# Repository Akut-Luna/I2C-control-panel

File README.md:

# I2C-control-panel
Modular panels using the MCP23017 IO expansion board and the I2C protocol.

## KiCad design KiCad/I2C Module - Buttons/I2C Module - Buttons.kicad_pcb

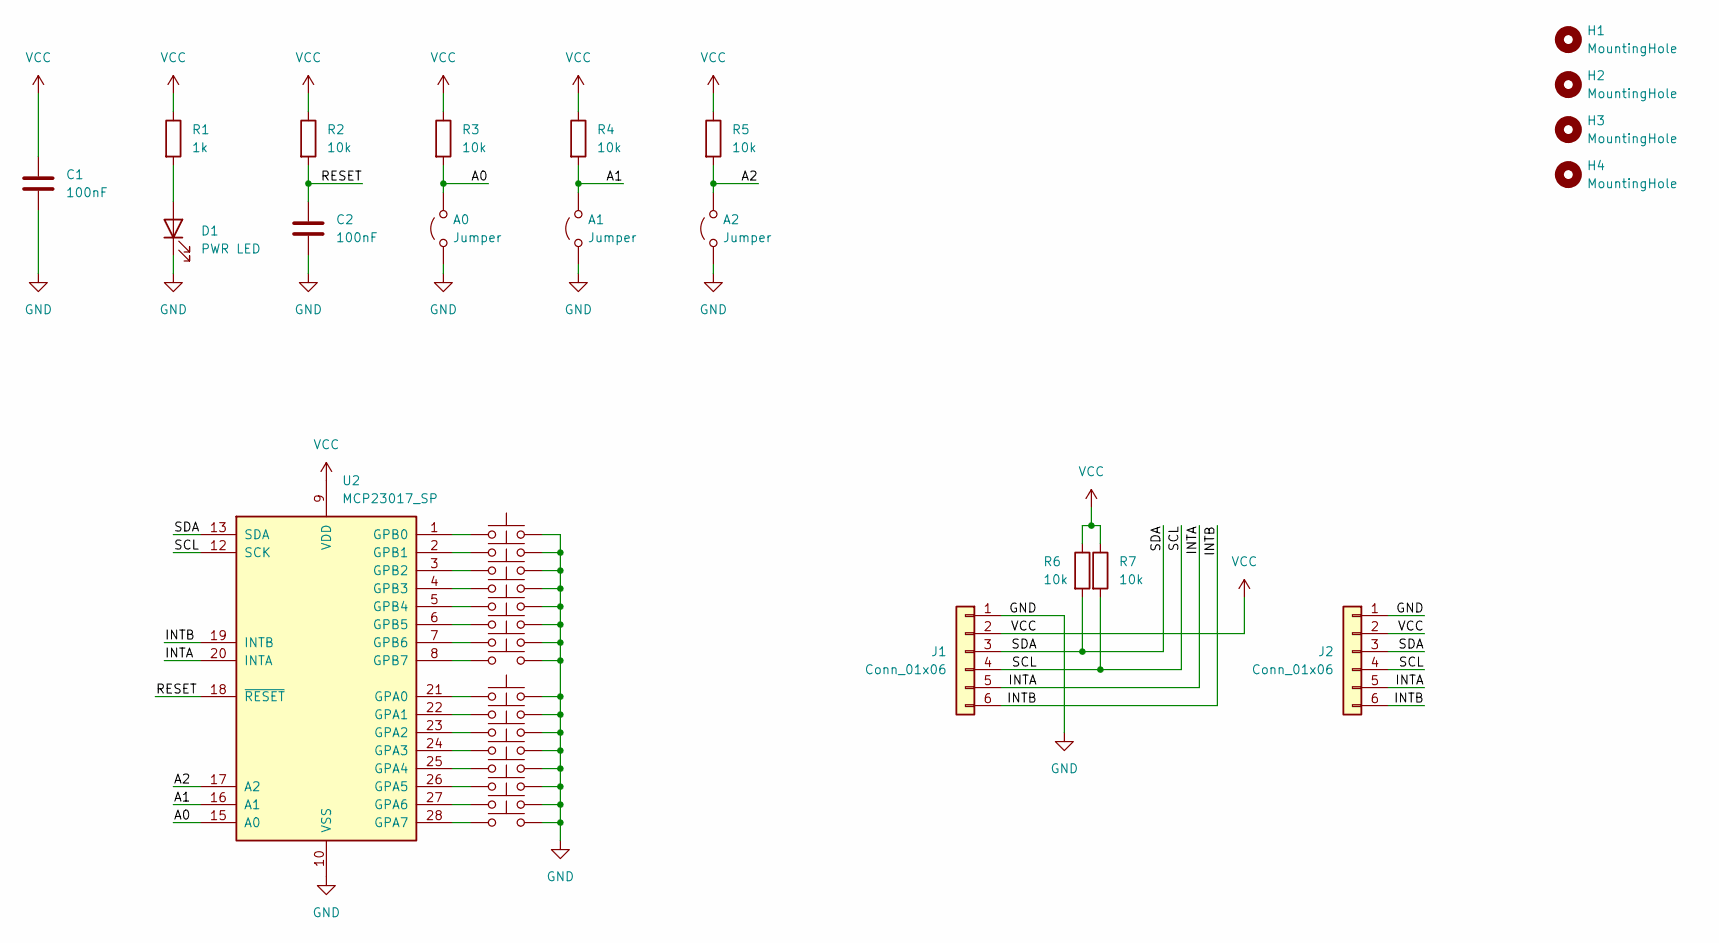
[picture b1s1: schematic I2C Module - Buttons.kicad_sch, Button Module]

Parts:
A0, A1, A2: Jumper; PinHeader_1x02_P2.54mm_Vertical
C1, C2: 100nF; C_Disc_D5.0mm_W2.5mm_P5.00mm
D1: PWR LED; LED_D5.0mm
H1, H2, H3, H4: MountingHole; MountingHole_3.5mm_Pad
J1, J2: Conn_01x06; JST_EH_S6B-EH_1x06_P2.50mm_Horizontal
R1: 1k; R_Axial_DIN0207_L6.3mm_D2.5mm_P10.16mm_Horizontal
R2, R3, R4, R5, R6, R7: 10k; R_Axial_DIN0207_L6.3mm_D2.5mm_P10.16mm_Horizontal
SW1, SW2, SW3, SW4, SW5, SW6, SW7, SW8, SW9, SW10, SW11, SW12, SW13, SW14, SW15, SW16: SW_Push; SW_SPST_Omron_B3F-50xx_3Dmodel
U2: MCP23017_SP; DIP-28_W7.62mm

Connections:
/A0: A0.2 (B), R3.2, U2.15 (A0)
/A1: A1.2 (B), R4.2, U2.16 (A1)
/A2: A2.2 (B), R5.2, U2.17 (A2)
/INTA: J1.5, J2.5, U2.20 (INTA)
/INTB: J1.6, J2.6, U2.19 (INTB)
/RESET: C2.1, R2.2, U2.18 (~RESET)
/SCL: J1.4, J2.4, R7.2, U2.12 (SCK)
/SDA: J1.3, J2.3, R6.2, U2.13 (SDA)
GND: A0.1 (A), A1.1 (A), A2.1 (A), C1.2, C2.2, D1.1 (K), J1.1, J2.1, SW1.2, SW2.2, SW3.2, SW4.2, SW5.2, SW6.2, SW7.2, SW8.2, SW9.2, SW10.2, SW11.2, SW12.2, SW13.2, SW14.2, SW15.2, SW16.2, U2.10 (VSS)
unnamed: D1.2 (A), R1.2
unnamed: SW4.1, U2.21 (GPA0)
unnamed: SW3.1, U2.22 (GPA1)
unnamed: SW2.1, U2.23 (GPA2)
unnamed: SW1.1, U2.24 (GPA3)
unnamed: SW5.1, U2.25 (GPA4)
unnamed: SW7.1, U2.26 (GPA5)
unnamed: SW6.1, U2.27 (GPA6)
unnamed: SW8.1, U2.28 (GPA7)
unnamed: SW9.1, U2.1 (GPB0)
unnamed: SW10.1, U2.2 (GPB1)
unnamed: SW11.1, U2.3 (GPB2)
unnamed: SW12.1, U2.4 (GPB3)
unnamed: SW13.1, U2.5 (GPB4)
unnamed: SW14.1, U2.6 (GPB5)
unnamed: SW15.1, U2.7 (GPB6)
unnamed: SW16.1, U2.8 (GPB7)
VCC: C1.1, J1.2, J2.2, R1.1, R2.1, R3.1, R4.1, R5.1, R6.1, R7.1, U2.9 (VDD)

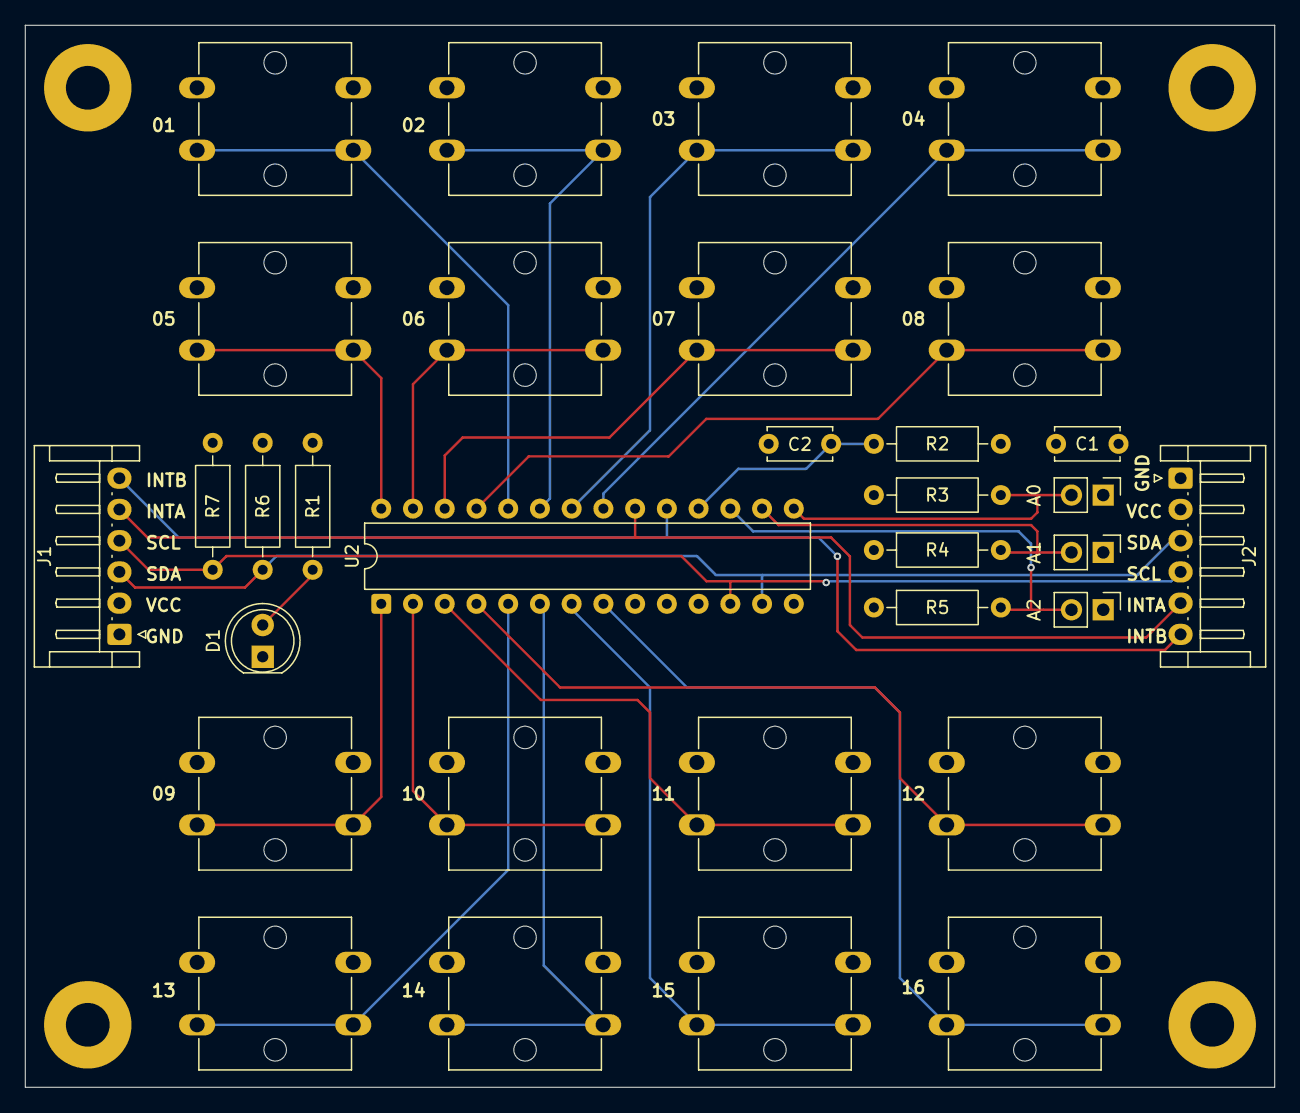
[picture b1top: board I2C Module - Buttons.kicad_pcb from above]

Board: 4 copper layers, 100.0 x 85.0 mm, 36 parts (0 on the bottom side), 27 nets.

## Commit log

2026-05-14 init commit
